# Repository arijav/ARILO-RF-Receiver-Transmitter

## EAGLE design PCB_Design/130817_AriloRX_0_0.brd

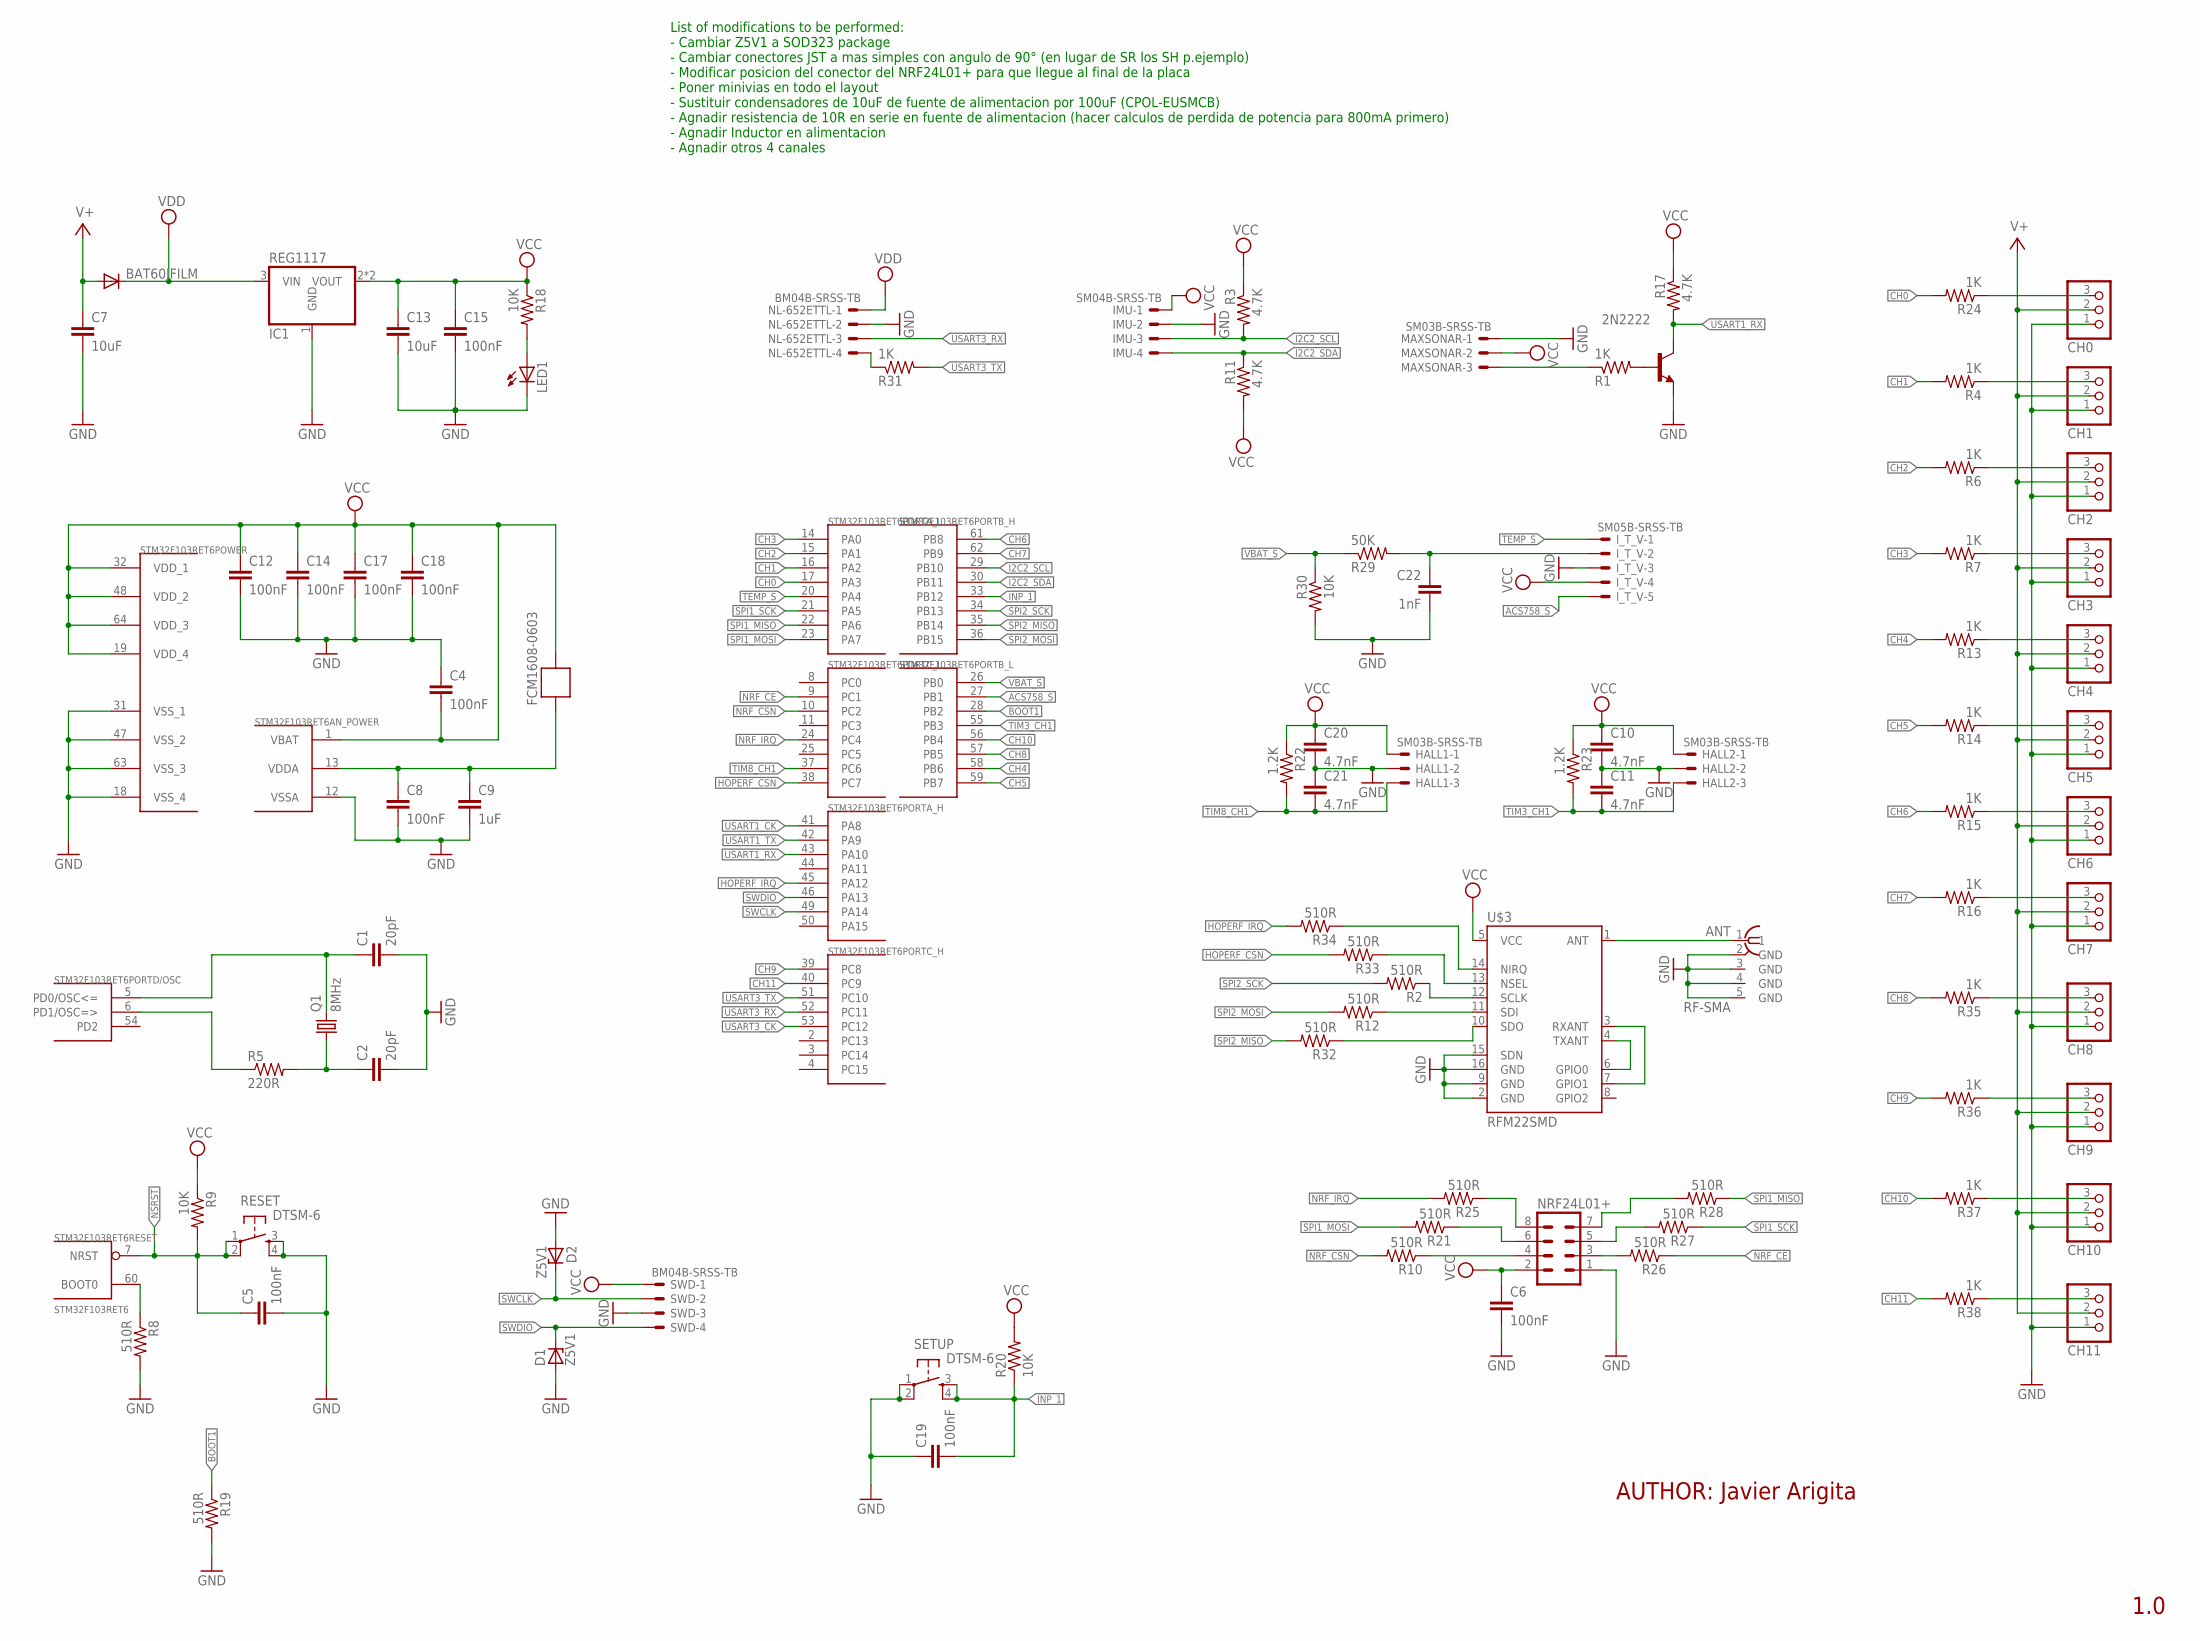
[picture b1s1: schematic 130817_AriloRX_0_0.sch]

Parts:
2N2222: MMBT2222ALT1-NPN-SOT23-BEC; SOT23-BEC
ANT: RF-SMA; BU-SMA-H
BAT60JFILM: DIODE-SOD323-R; SOD323-R
C1, C2: 20pF; C0805
C4, C5, C6, C8, C12, C14, C15, C17, C18, C19: 100nF; C0805
C7, C13: 10uF; C3216
C9: 1uF; C3216
C10, C11, C20, C21: 4.7nF; C0805
C22: 1nF; C0805
CH0, CH1, CH2, CH3, CH4, CH5, CH6, CH7, CH8, CH9, CH10, CH11: PINHD-1X3; 1X03
D1, D2: Z5V1; SOD80C
FCM1608-0603: FERRITE-BEAD; R0603
HALL1, HALL2: SM03B-SRSS-TB
IC1: REG1117; SOT223
IMU: SM04B-SRSS-TB
I_T_V: SM05B-SRSS-TB
LED1: LED0805; CHIPLED_0805
MAXSONAR: SM03B-SRSS-TB
NL-652ETTL: BM04B-SRSS-TB
NRF24L01+: MA04-2
Q1: 8MHz; SM49
R1, R4, R6, R7, R13, R14, R15, R16, R24, R31, R35, R36, R37, R38: 1K; R0805
R2, R8, R10, R12, R19, R21, R25, R26, R27, R28, R32, R33, R34: 510R; R0805
R3, R11, R17: 4.7K; R0805
R5: 220R; R0805
R9, R18, R20, R30: 10K; R0805
R22, R23: 1.2K; R0805
R29: 50K; R0805
RESET: DTSM-6
SETUP: DTSM-6
STM32F103RET6: STM32F103RET6; TQFP64
SWD: BM04B-SRSS-TB
U$3: RFM22SMD; RFM22-XXX-S2

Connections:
ACS758_S: I_T_V.5, STM32F103RET6.27 (PB1)
BOOT1: R19.1, STM32F103RET6.28 (PB2)
CH0: R24.2, STM32F103RET6.17 (PA3)
CH1: R4.2, STM32F103RET6.16 (PA2)
CH2: R6.2, STM32F103RET6.15 (PA1)
CH3: R7.2, STM32F103RET6.14 (PA0)
CH4: R13.2, STM32F103RET6.58 (PB6)
CH5: R14.2, STM32F103RET6.59 (PB7)
CH6: R15.2, STM32F103RET6.61 (PB8)
CH7: R16.2, STM32F103RET6.62 (PB9)
CH8: R35.2, STM32F103RET6.57 (PB5)
CH9: R36.2, STM32F103RET6.39 (PC8)
CH10: R37.2, STM32F103RET6.56 (PB4)
CH11: R38.2, STM32F103RET6.40 (PC9)
GND: 2N2222.E, ANT.2 (GND), ANT.3 (GND), ANT.4 (GND), ANT.5 (GND), C1.2, C2.2, C4.1, C5.2, C6.2, C7.2, C8.2, C9.2, C10.2, C11.1, C12.2, C13.2, C14.2, C15.2, C17.2, C18.2, C19.1, C20.2, C21.1, C22.2, CH0.1, CH1.1, CH2.1, CH3.1, CH4.1, CH5.1, CH6.1, CH7.1, CH8.1, CH9.1, CH10.1, CH11.1, D1.A, D2.A, HALL1.2, HALL2.2, IC1.1 (GND), IMU.2, I_T_V.3, LED1.C, MAXSONAR.1, NL-652ETTL.2, NRF24L01+.1, R8.2, R19.2, R30.2, RESET.3, RESET.4, SETUP.1, SETUP.2, STM32F103RET6.12 (VSSA), STM32F103RET6.18 (VSS_4), STM32F103RET6.31 (VSS_1), STM32F103RET6.47 (VSS_2), STM32F103RET6.63 (VSS_3), SWD.3, U$3.2 (GND), U$3.9 (GND), U$3.15 (SDN), U$3.16 (GND)
HOPERF_CSN: R33.2, STM32F103RET6.38 (PC7)
HOPERF_IRQ: R34.2, STM32F103RET6.45 (PA12)
I2C2_SCL: IMU.3, R3.2, STM32F103RET6.29 (PB10)
I2C2_SDA: IMU.4, R11.1, STM32F103RET6.30 (PB11)
INP_1: C19.2, R20.1, SETUP.3, SETUP.4, STM32F103RET6.33 (PB12)
unnamed: C1.1, Q1.2, STM32F103RET6.5 (PD0/OSC<=)
unnamed: R5.1, STM32F103RET6.6 (PD1/OSC=>)
unnamed: C2.1, Q1.1, R5.2
unnamed: R8.1, STM32F103RET6.60 (BOOT0)
unnamed: U$3.3 (RXANT), U$3.7 (GPIO1)
unnamed: U$3.4 (TXANT), U$3.6 (GPIO0)
unnamed: R2.1, U$3.12 (SCLK)
unnamed: R12.1, U$3.11 (SDI)
unnamed: CH0.3, R24.1
unnamed: LED1.A, R18.2
unnamed: NL-652ETTL.4, R31.1
unnamed: R32.1, U$3.10 (SDO)
unnamed: CH8.3, R35.1
unnamed: MAXSONAR.3, R1.1
unnamed: C22.1, I_T_V.2, R29.2
unnamed: 2N2222.B, R1.2
unnamed: C8.1, C9.1, FCM1608-0603.2, STM32F103RET6.13 (VDDA)
unnamed: NRF24L01+.4, R10.1
unnamed: NRF24L01+.3, R26.2
unnamed: ANT.1, U$3.1 (ANT)
unnamed: CH2.3, R6.1
unnamed: R34.1, U$3.14 (NIRQ)
unnamed: CH4.3, R13.1
unnamed: R33.1, U$3.13 (NSEL)
unnamed: CH9.3, R36.1
unnamed: CH10.3, R37.1
unnamed: CH11.3, R38.1
unnamed: CH3.3, R7.1
unnamed: CH6.3, R15.1
unnamed: CH5.3, R14.1
unnamed: CH7.3, R16.1
unnamed: NRF24L01+.5, R27.2
unnamed: NRF24L01+.6, R21.1
unnamed: NRF24L01+.8, R25.1
unnamed: NRF24L01+.7, R28.2
unnamed: CH1.3, R4.1
NRF_CE: R26.1, STM32F103RET6.9 (PC1)
NRF_CSN: R10.2, STM32F103RET6.10 (PC2)
NRF_IRQ: R25.2, STM32F103RET6.24 (PC4)
NSRST: C5.1, R9.2, RESET.1, RESET.2, STM32F103RET6.7 (NRST)
SPI1_MISO: R28.1, STM32F103RET6.22 (PA6)
SPI1_MOSI: R21.2, STM32F103RET6.23 (PA7)
SPI1_SCK: R27.1, STM32F103RET6.21 (PA5)
SPI2_MISO: R32.2, STM32F103RET6.35 (PB14)
SPI2_MOSI: R12.2, STM32F103RET6.36 (PB15)
SPI2_SCK: R2.2, STM32F103RET6.34 (PB13)
SWCLK: D2.C, STM32F103RET6.49 (PA14), SWD.2
SWDIO: D1.C, STM32F103RET6.46 (PA13), SWD.4
TEMP_S: I_T_V.1, STM32F103RET6.20 (PA4)
TIM3_CH1: C11.2, HALL2.3, R23.2, STM32F103RET6.55 (PB3)
TIM8_CH1: C21.2, HALL1.3, R22.2, STM32F103RET6.37 (PC6)
USART1_CK: STM32F103RET6.41 (PA8)
USART1_RX: 2N2222.C, R17.2, STM32F103RET6.43 (PA10)
USART1_TX: STM32F103RET6.42 (PA9)
USART3_CK: STM32F103RET6.53 (PC12)
USART3_RX: NL-652ETTL.3, STM32F103RET6.52 (PC11)
USART3_TX: R31.2, STM32F103RET6.51 (PC10)
V+: BAT60JFILM.A, C7.1, CH0.2, CH1.2, CH2.2, CH3.2, CH4.2, CH5.2, CH6.2, CH7.2, CH8.2, CH9.2, CH10.2, CH11.2
VBAT_S: R29.1, R30.1, STM32F103RET6.26 (PB0)
VCC: C4.2, C6.1, C10.1, C12.1, C13.1, C14.1, C15.1, C17.1, C18.1, C20.1, FCM1608-0603.1, HALL1.1, HALL2.1, IC1.2 (VOUT), IC1.4 (VOUT), IMU.1, I_T_V.4, MAXSONAR.2, NRF24L01+.2, R3.1, R9.1, R11.2, R17.1, R18.1, R20.2, R22.1, R23.1, STM32F103RET6.1 (VBAT), STM32F103RET6.19 (VDD_4), STM32F103RET6.32 (VDD_1), STM32F103RET6.48 (VDD_2), STM32F103RET6.64 (VDD_3), SWD.1, U$3.5 (VCC)
VDD: BAT60JFILM.C, IC1.3 (VIN), NL-652ETTL.1

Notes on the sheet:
AUTHOR: Javier Arigita
1.0
List of modifications to be performed: - Cambiar Z5V1 a SOD323 package - Cambiar conectores JST a mas simples con angulo de 90° (en lugar de SR los SH p.ejemplo) - Modificar posicion del conector del NRF24L01+ para que llegue al final de la placa - Poner minivias en todo el layout - Sustituir conde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

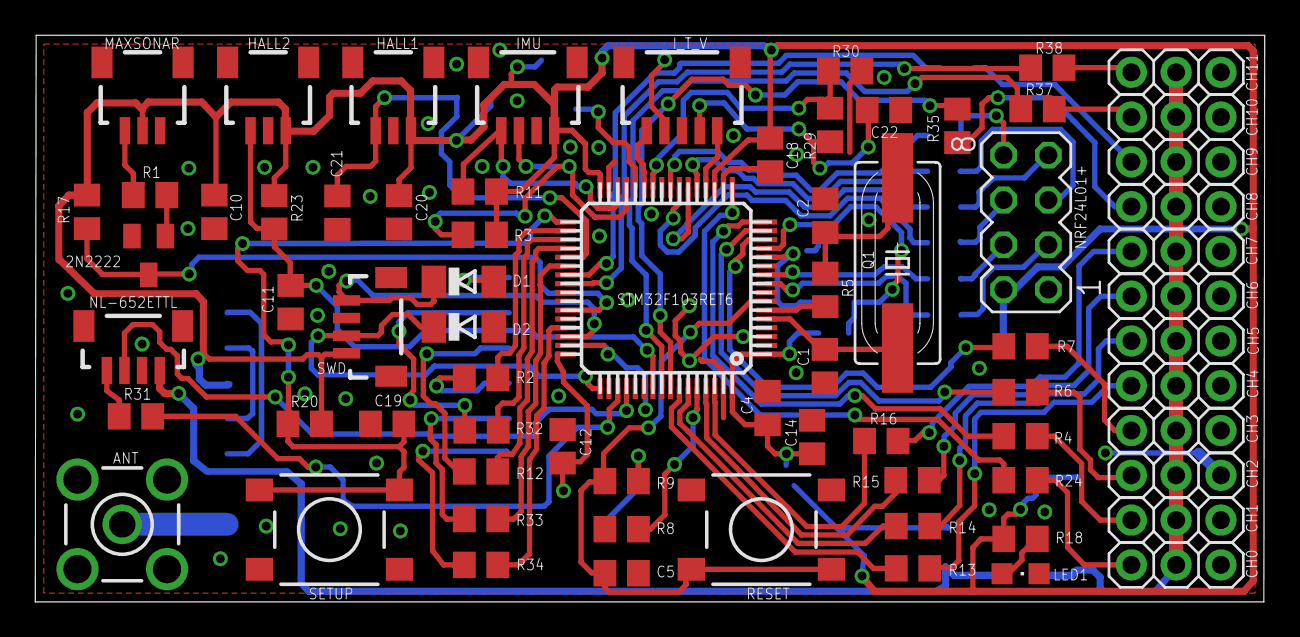
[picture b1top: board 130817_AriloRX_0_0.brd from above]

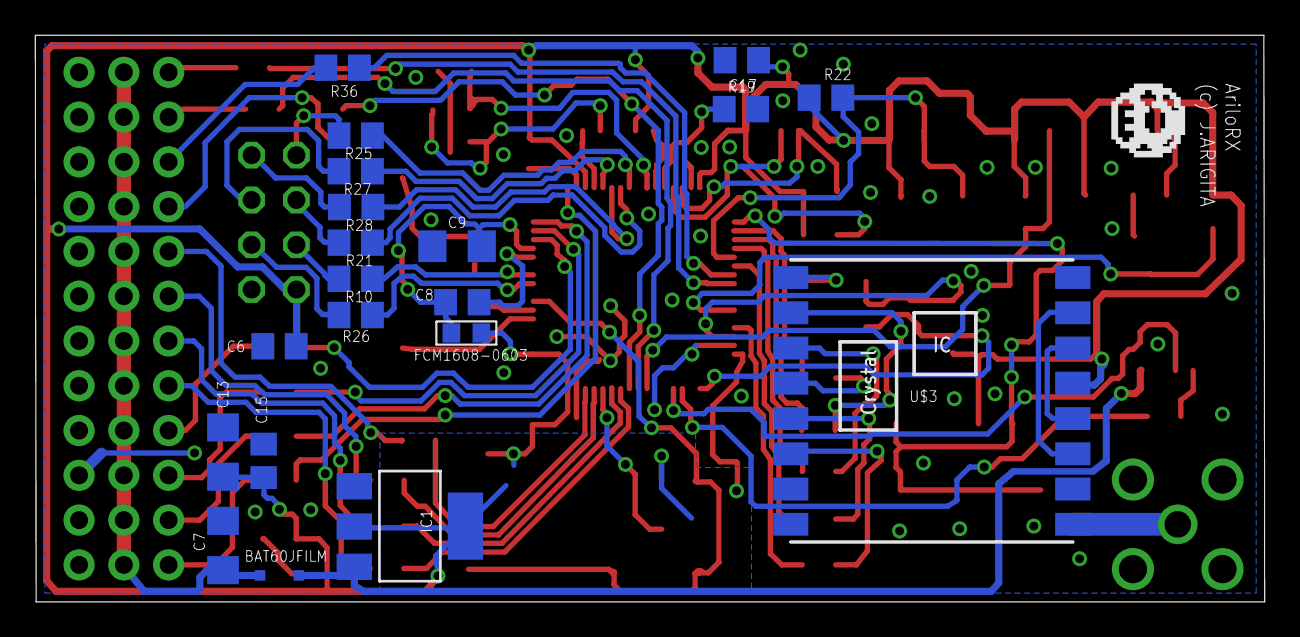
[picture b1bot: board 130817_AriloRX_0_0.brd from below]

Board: 2 copper layers, 69.7 x 32.1 mm, 91 parts (20 on the bottom side), 78 nets.

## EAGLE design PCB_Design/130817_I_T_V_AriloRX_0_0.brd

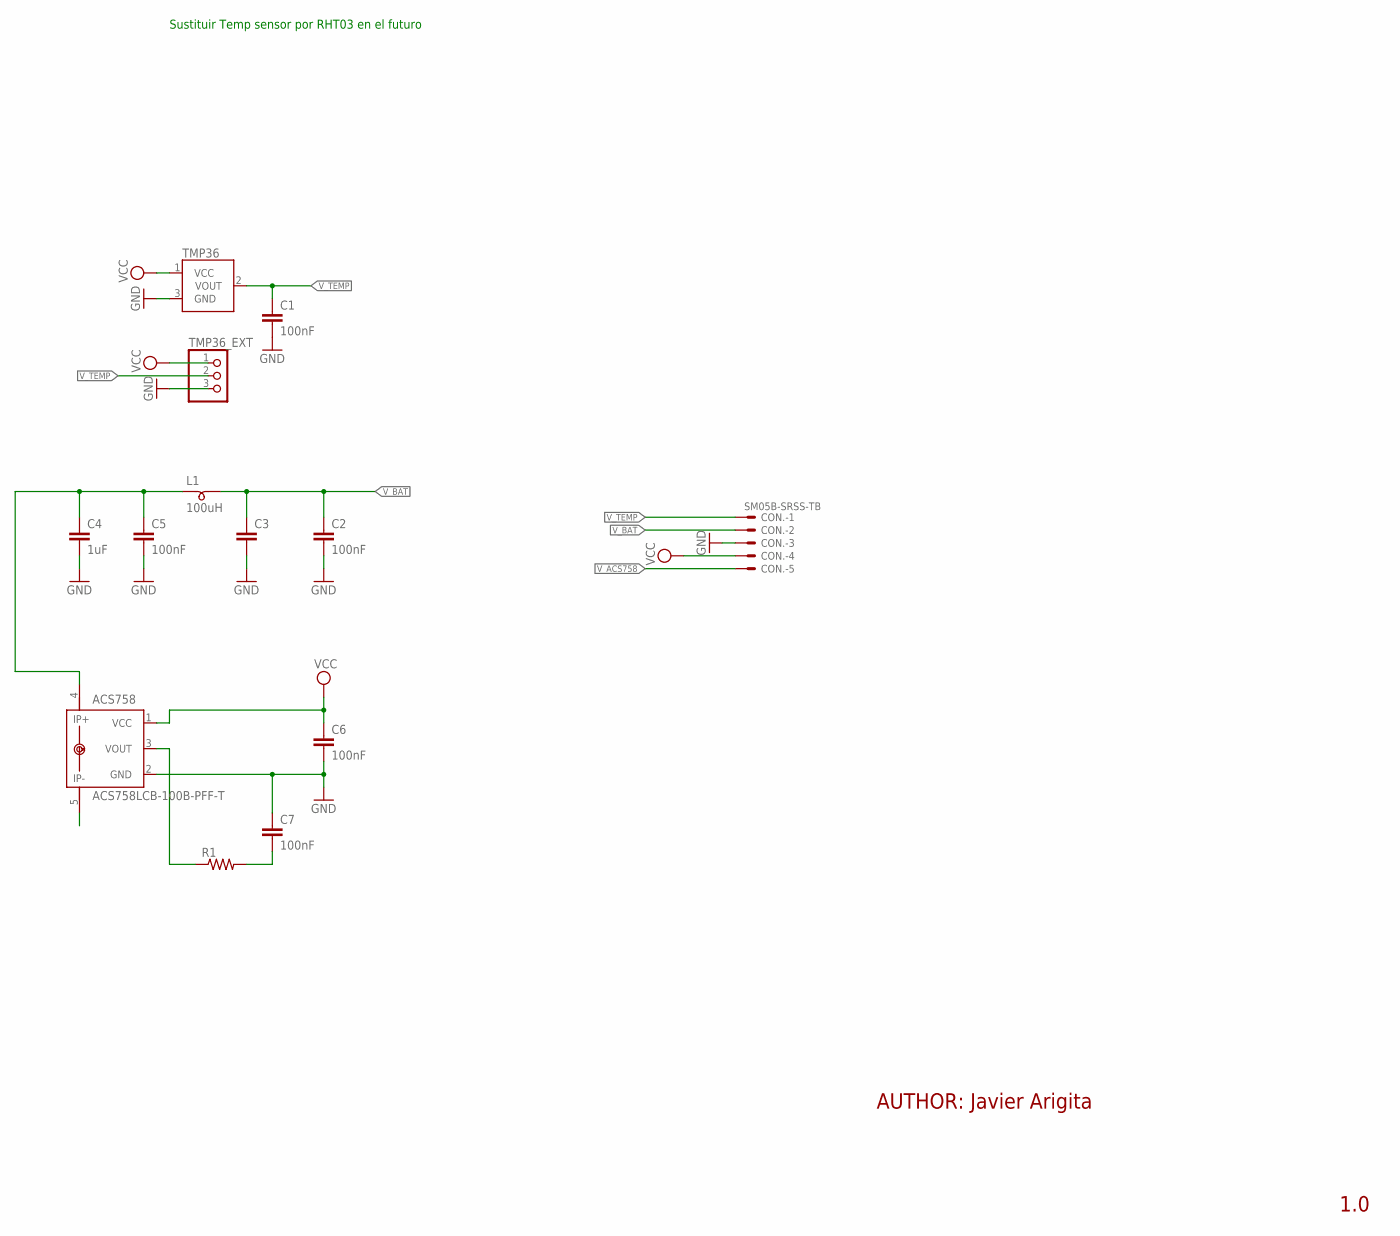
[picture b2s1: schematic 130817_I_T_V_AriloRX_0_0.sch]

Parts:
ACS758: ACS758LCB-100B-PFF-T; CB-PFF
C1, C2, C5, C6, C7: 100nF; C0805
C3: C-EUC3216; C3216
C4: 1uF; C3216
CON.: SM05B-SRSS-TB
L1: 100uH; SM-B5
R1: RESISTOR0805; R0805
TMP36: TMP36GT9; TO-92
TMP36_EXT: PINHD-1X3; 1X03

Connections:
GND: ACS758.2 (GND), C1.2, C2.2, C3.2, C4.2, C5.2, C6.2, C7.1, CON..3, TMP36.3 (GND), TMP36_EXT.3
unnamed: ACS758.4 (IP+), C4.1, C5.1, L1.1
unnamed: C7.2, R1.2
unnamed: ACS758.3 (VOUT), R1.1
VCC: ACS758.1 (VCC), C6.1, CON..4, TMP36.1 (VCC), TMP36_EXT.1
V_ACS758: CON..5
V_BAT: C2.1, C3.1, CON..2, L1.2
V_TEMP: C1.1, CON..1, TMP36.2 (VOUT), TMP36_EXT.2

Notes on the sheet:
AUTHOR: Javier Arigita
1.0
Sustituir Temp sensor por RHT03 en el futuro

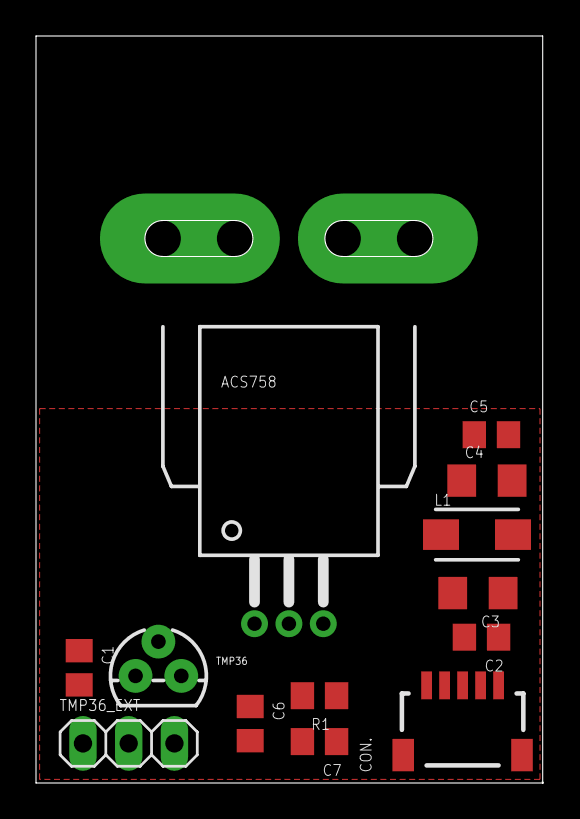
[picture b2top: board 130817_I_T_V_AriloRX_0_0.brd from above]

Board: 2 copper layers, 28.1 x 41.5 mm, 13 parts (0 on the bottom side), 7 nets.

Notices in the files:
parts and their libraries:
SparkFun-RF: Licensing: CC v3.0 Share-Alike You are welcome to use this library for commercial purposes.
